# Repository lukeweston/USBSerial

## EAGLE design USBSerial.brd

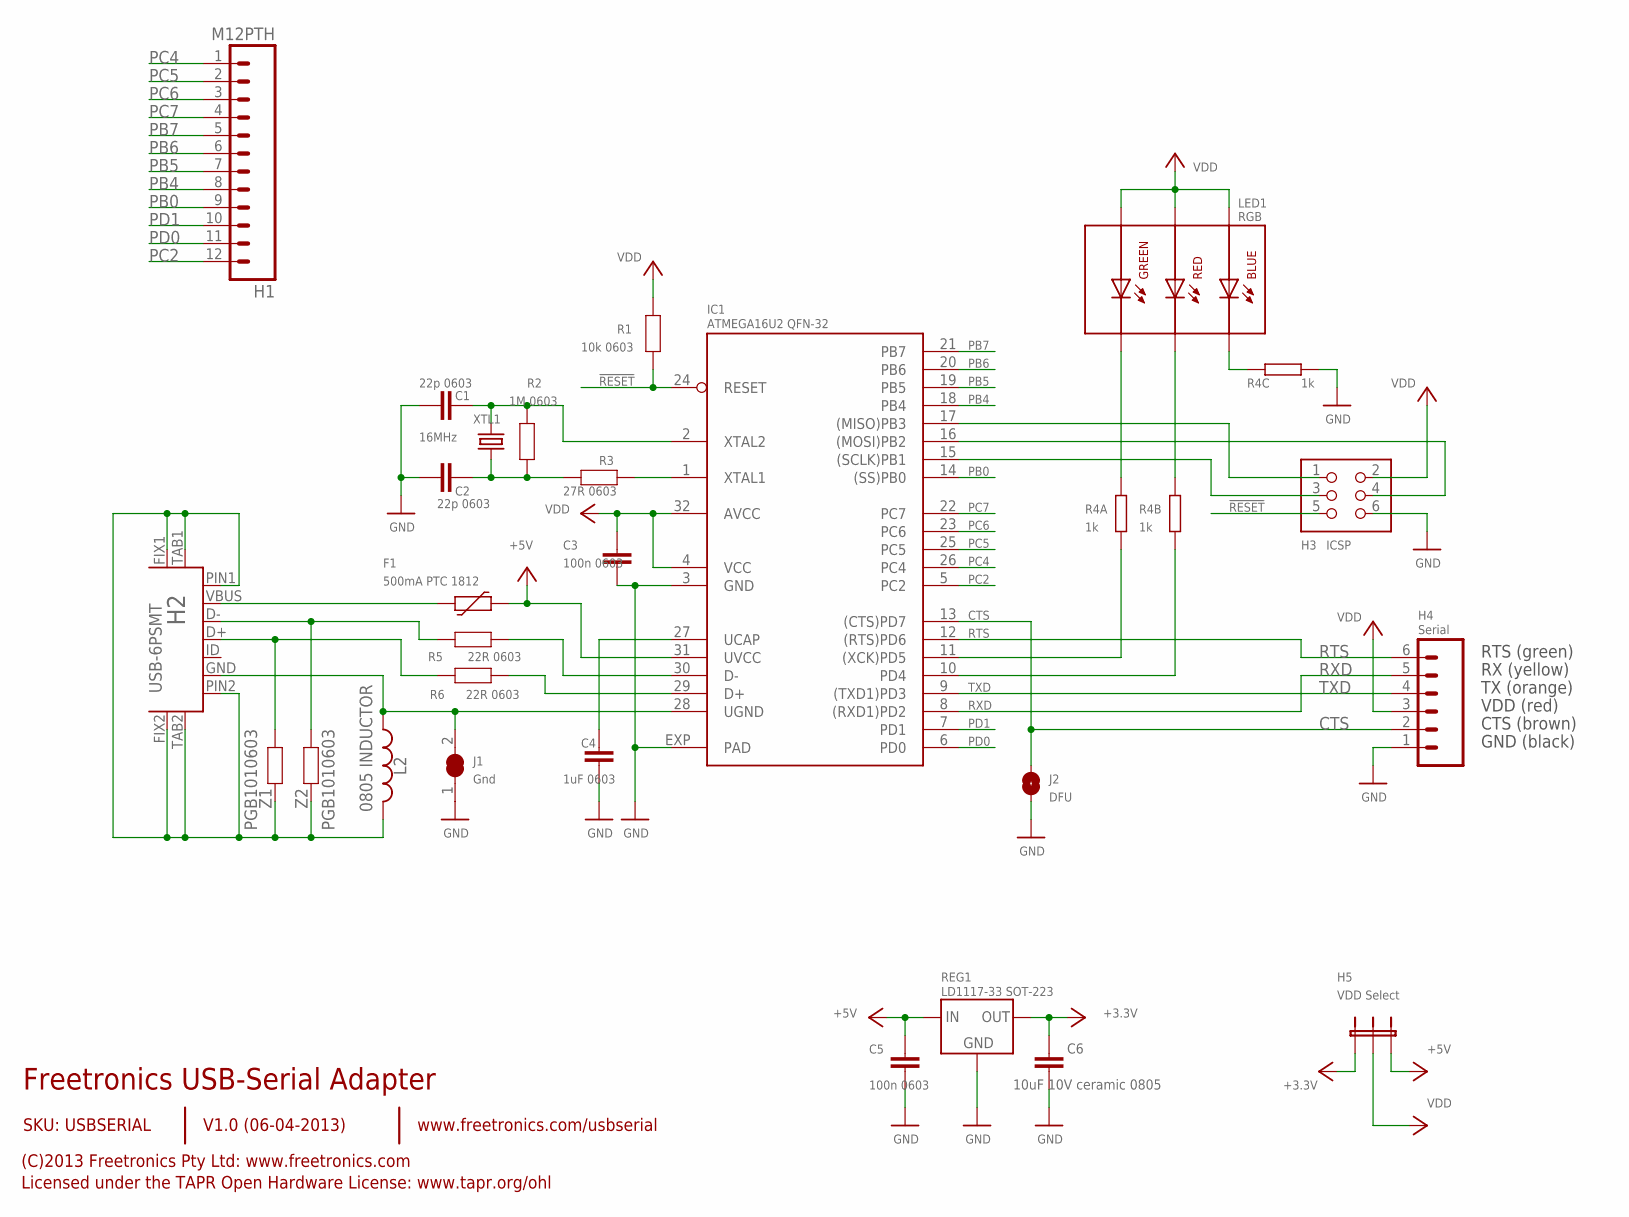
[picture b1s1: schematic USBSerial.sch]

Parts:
C1, C2: 22p 0603; 0603
C3, C5: 100n 0603; 0603
C4: 1uF 0603; 0603
C6: 10uF 10V ceramic 0805; C0805
F1: 500mA PTC 1812; 1812
H1: M12PTH; 1X12
H2: USB-6PSMT; USB-MICROB-MB05PMXX
H3: ICSP; HEADER_2X3
H4: Serial; 1X06
H5: VDD Select; JUMPER_SPDT
IC1: ATMEGA16U2 QFN-32; ATMEL_QFN32
J1: Gnd; SJC
J2: DFU; SJ
L2: 0805 INDUCTOR; 0805-LARGE
LED1: RGB; 19-337
R1: 10k 0603; 0603
R2: 1M 0603; 0603
R3: 27R 0603; 0603
R4: 1k; CAY16
R5, R6: 22R 0603; 0603
REG1: LD1117-33 SOT-223; SOT-223
XTL1: 16MHz; HC49US
Z1, Z2: PGB1010603; 0603

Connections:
!RESET: H3.5, IC1.24 (RESET), R1.1
+3V3: C6.1, H5.1, REG1.2 (OUT), REG1.4 (OUT)
+5V: C5.1, F1.2, H5.3, IC1.31 (UVCC), REG1.3 (IN)
CTS: H4.2, IC1.13 ((CTS)PD7), J2.2
GND: C1.1, C2.1, C3.2, C4.2, C5.2, C6.2, H3.6, H4.1, IC1.3 (GND), IC1.EXP (PAD), J1.1, J2.1, R4.6 (2), REG1.1 (GND)
MISO: H3.1, IC1.17 ((MISO)PB3)
MOSI: H3.4, IC1.16 ((MOSI)PB2)
unnamed: H2.GND, IC1.28 (UGND), J1.2, L2.1
unnamed: IC1.1 (XTAL1), R3.1
unnamed: LED1.2 (C-R), R4.2 (1)
unnamed: LED1.1 (C-B), R4.3 (1)
unnamed: LED1.3 (C-G), R4.1
unnamed: H2.FIX1, H2.FIX2, H2.PIN1, H2.PIN2, H2.TAB1, H2.TAB2, L2.2, Z1.2, Z2.2
unnamed: H2.D+, R6.2, Z1.1
unnamed: H2.D-, R5.2, Z2.1
unnamed: C1.2, IC1.2 (XTAL2), R2.2, XTL1.2
unnamed: C2.2, R2.1, R3.2, XTL1.1
unnamed: F1.1, H2.VBUS
unnamed: C4.1, IC1.27 (UCAP)
PB0: H1.9, IC1.14 ((SS)PB0)
PB4: H1.8, IC1.18 (PB4)
PB5: H1.7, IC1.19 (PB5)
PB6: H1.6, IC1.20 (PB6)
PB7: H1.5, IC1.21 (PB7)
PC2: H1.12, IC1.5 (PC2)
PC4: H1.1, IC1.26 (PC4)
PC5: H1.2, IC1.25 (PC5)
PC6: H1.3, IC1.23 (PC6)
PC7: H1.4, IC1.22 (PC7)
PD0: H1.11, IC1.6 (PD0)
PD1: H1.10, IC1.7 (PD1)
RD+: IC1.29 (D+), R6.1
RD-: IC1.30 (D-), R5.1
RTS: H4.6, IC1.12 ((RTS)PD6)
RXD: H4.5, IC1.8 ((RXD1)PD2)
RXLED: IC1.10 (PD4), R4.7 (2)
SCK: H3.3, IC1.15 ((SCLK)PB1)
TXD: H4.4, IC1.9 ((TXD1)PD3)
TXLED: IC1.11 ((XCK)PD5), R4.8 (2)
VDD: C3.1, H3.2, H4.3, H5.2, IC1.4 (VCC), IC1.32 (AVCC), LED1.4 (A-B), LED1.5 (A-R), LED1.6 (A-G), R1.2

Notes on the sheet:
Freetronics USB-Serial Adapter
V1.0 (06-04-2013)
SKU: USBSERIAL
(C)2013 Freetronics Pty Ltd: www.freetronics.com
Licensed under the TAPR Open Hardware License: www.tapr.org/ohl
www.freetronics.com/usbserial
RTS (green)
RX (yellow)
TX (orange)
VDD (red)
CTS (brown)
GND (black)

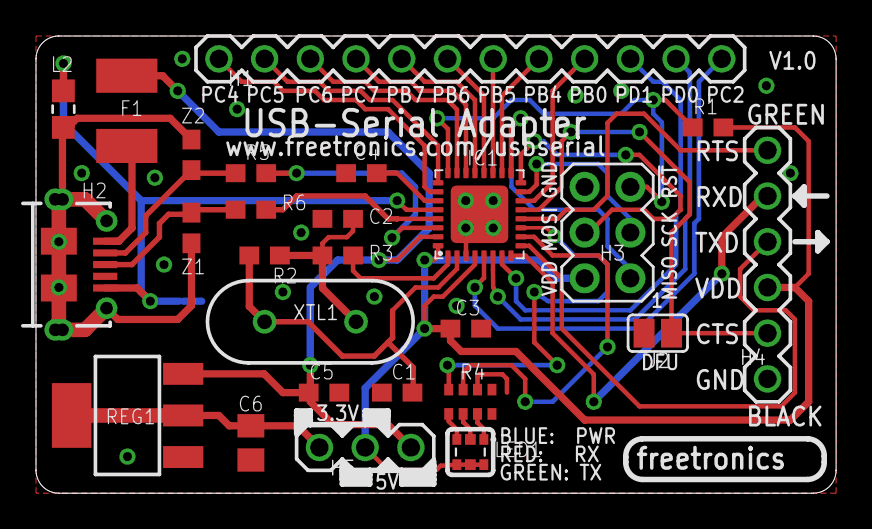
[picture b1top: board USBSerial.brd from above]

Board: 2 copper layers, 44.5 x 25.4 mm, 27 parts (1 on the bottom side), 40 nets.

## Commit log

2013-04-06 Preparation for v1.0 release

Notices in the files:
parts and their libraries:
freetronics-original: Licensing: CC v3.0 Share-Alike You are welcome to use this library for commercial purposes.
